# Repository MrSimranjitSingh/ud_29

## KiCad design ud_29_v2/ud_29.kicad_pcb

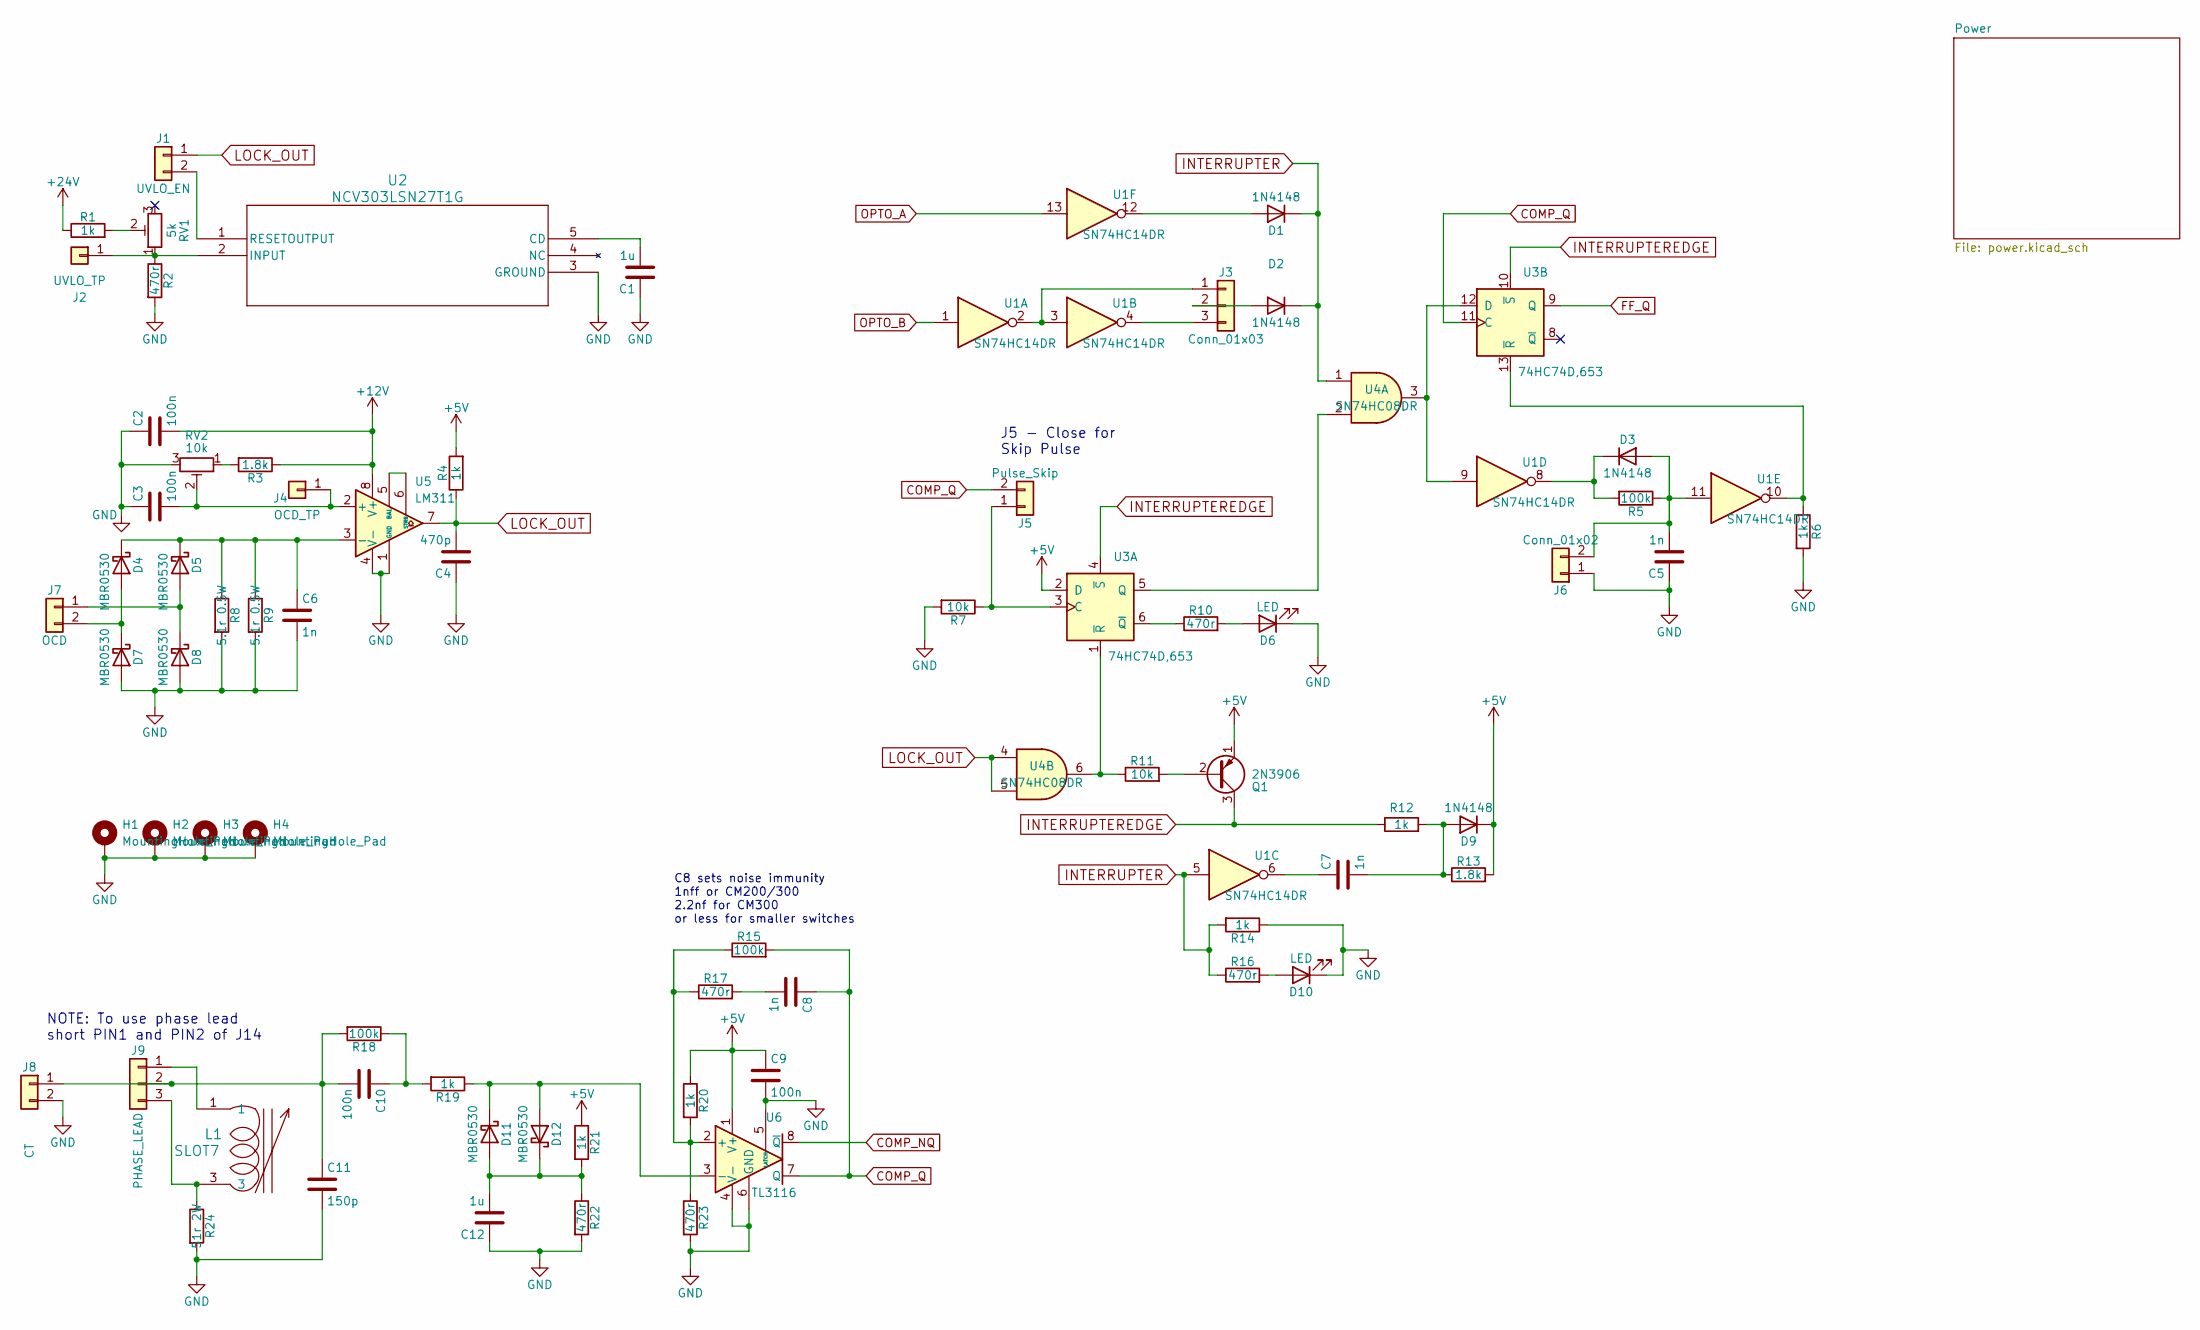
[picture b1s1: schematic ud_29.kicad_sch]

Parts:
C1, C12: 1u; C_1206_3216Metric_Pad1.33x1.80mm_HandSolder; Part Number CL21B105KBFNNNG
C2, C3, C9, C10: 100n; C_1206_3216Metric_Pad1.33x1.80mm_HandSolder; Part Number KGM21NR71H104KT
C4: 470p; C_1206_3216Metric_Pad1.33x1.80mm_HandSolder; Part Number C0805C471K5RAC7800
C5, C6, C7, C8: 1n; C_1206_3216Metric_Pad1.33x1.80mm_HandSolder; Part Number CL21B102KCANNNC
C11: 150p; C_1206_3216Metric_Pad1.33x1.80mm_HandSolder; Part Number C0805C151J5GAC7800
D1, D2, D3, D9: 1N4148; D_SOD-123; Part Number 1N4148WGW
D4, D5, D7, D8, D11, D12: MBR0530; D_SOD-123; Part Number MBR0530-TP
D6, D10: LED; LED_D5.0mm
H1, H2, H3, H4: MountingHole_Pad; MountingHole_3.5mm_Pad_TopBottom
J1: UVLO_EN; PinHeader_1x02_P2.54mm_Vertical
J2: UVLO_TP; PinHeader_1x01_P2.54mm_Vertical
J3: Conn_01x03; PinHeader_1x03_P2.54mm_Vertical
J4: OCD_TP; PinHeader_1x01_P2.54mm_Vertical
J5: Pulse_Skip; PinHeader_1x02_P2.54mm_Vertical
J6: Conn_01x02; PinHeader_1x02_P2.54mm_Vertical
J7: OCD; TerminalBlock_bornier-2_P5.08mm; Part Number EBB-02-D-BL
J8: CT; TerminalBlock_bornier-2_P5.08mm; Part Number EBB-02-D-BL
J9: PHASE_LEAD; PinHeader_1x03_P2.54mm_Vertical
L1: SLOT7; CoilCraft_Slot_7
Q1: 2N3906; TO-92
R1, R4, R6, R12, R14, R19, R20, R21: 1k; R_1206_3216Metric_Pad1.30x1.75mm_HandSolder; Part Number RNCP0805FTD1K00
R2, R10, R16, R17, R22, R23: 470r; R_1206_3216Metric_Pad1.30x1.75mm_HandSolder; Part Number RK73H2ATTD4700F
R3, R13: 1.8k; R_1206_3216Metric_Pad1.30x1.75mm_HandSolder; Part Number RK73B2ATTD182J
R5, R15, R18: 100k; R_1206_3216Metric_Pad1.30x1.75mm_HandSolder; Part Number RK73H2ATTD1003F
R7, R11: 10k; R_1206_3216Metric_Pad1.30x1.75mm_HandSolder; Part Number RK73H2ATTD1002F
R8, R9: 5.1r 0.5W; R_1206_3216Metric_Pad1.30x1.75mm_HandSolder; Part Number ESR10EZPJ5R1
R24: 51r 2W; R_1206_3216Metric_Pad1.30x1.75mm_HandSolder; Part Number CRM2512-JW-510ELF
RV1: 5k; Potentiometer_Bourns_3296W_Vertical
RV2: 10k; Potentiometer_Bourns_3296W_Vertical
U1: SN74HC14DR; SOIC-14_3.9x8.7mm_P1.27mm; Part Number SN74HC14DR
U2: NCV303LSN27T1G; TSOT-23-5_HandSoldering; Part Number NCV303LSN27T1G
U3: 74HC74D,653; SOIC-14_3.9x8.7mm_P1.27mm; Part Number 74HC74D,653
U4: SN74HC08DR; SOIC-14_3.9x8.7mm_P1.27mm; Part Number SN74HC08DR
U5: LM311; SOIC-8_3.9x4.9mm_P1.27mm; Part Number LM311DR
U6: TL3116; SOIC-8_3.9x4.9mm_P1.27mm; Part Number TL3116CD

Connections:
+5V: C9.1, D9.1 (K), Q1.1 (E), R4.2, R13.2, R20.1, R21.1, U3.2 (D), U6.1 (V+); also elsewhere on the board
+12V: C2.2, R3.1, U5.8 (V+); also elsewhere on the board
+24V: R1.1; also elsewhere on the board
COMP_NQ: U6.8 (~Q); also elsewhere on the board
COMP_Q: C8.1, J5.2, R15.2, U3.11 (C), U6.7 (Q); also elsewhere on the board
FF_Q: U3.9 (Q); also elsewhere on the board
GND: C1.1, C2.1, C3.1, C4.1, C5.1, C6.2, C9.2, C11.2, C12.1, D6.1 (K), D7.2 (A), D8.2 (A), D10.1 (K), H1.1, H2.1, H3.1, H4.1, J6.1, J8.2, R2.2, R6.2, R7.2, R8.2, R9.2, R14.1, R22.2, R23.2, R24.2, RV2.3, U2.3 (GROUND), U5.1 (GND), U5.4 (V-), U6.4 (V-), U6.5 (LATCH), U6.6 (GND); also elsewhere on the board
INTERRUPTER: D1.1 (K), D2.1 (K), R14.2, R16.1, U1.5, U4.1
INTERRUPTEREDGE: Q1.3 (C), R12.1, U3.4 (~S), U3.10 (~S)
LOCK_OUT: C4.2, J1.1, R4.1, U4.4, U4.5, U5.7
unnamed: C7.1, U1.6
unnamed: C8.2, R17.2
unnamed: C10.1, R18.1, R19.2
unnamed: D1.2 (A), U1.12
unnamed: D2.2 (A), J3.2
unnamed: C5.2, D3.2 (A), J6.2, R5.1, U1.11
unnamed: D3.1 (K), R5.2, U1.8
unnamed: D4.2 (A), D7.1 (K), J7.2
unnamed: C6.1, D4.1 (K), D5.1 (K), R8.1, R9.1, U5.3 (-)
unnamed: D5.2 (A), D8.1 (K), J7.1
unnamed: D6.2 (A), R10.2
unnamed: C7.2, D9.2 (A), R12.2, R13.1
unnamed: D10.2 (A), R16.2
unnamed: C12.2, D11.2 (A), D12.1 (K), R21.2, R22.1
unnamed: D11.1 (K), D12.2 (A), R19.1, U6.3 (-)
unnamed: J1.2, U2.1 (RESETOUTPUT)
unnamed: J2.1, R2.1, RV1.1, U2.2 (INPUT)
unnamed: J3.1, U1.2, U1.3
unnamed: J3.3, U1.4
unnamed: C3.2, J4.1, RV2.2, U5.2 (+)
unnamed: J5.1, R7.1, U3.3 (C)
unnamed: C10.2, C11.1, J8.1, J9.2, R18.2
unnamed: J9.1, L1.1
unnamed: J9.3, L1.3, R24.1
unnamed: Q1.2 (B), R11.2
unnamed: R1.2, RV1.2
unnamed: R3.2, RV2.1
unnamed: C1.2, U2.5 (CD)
unnamed: U3.5 (Q), U4.2
unnamed: R10.1, U3.6 (~Q)
unnamed: R11.1, U3.1 (~R), U4.6
unnamed: U1.9, U3.12 (D), U4.3
unnamed: R6.1, U1.10, U3.13 (~R)
unnamed: U5.5 (BAL), U5.6 (STRB)
unnamed: R15.1, R17.1, R20.2, R23.1, U6.2 (+)
OPTO_A: U1.13; also elsewhere on the board
OPTO_B: U1.1; also elsewhere on the board

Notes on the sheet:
C8 sets noise immunity 1nff or CM200/300 2.2nf for CM300 or less for smaller switches
NOTE: To use phase lead short PIN1 and PIN2 of J14
J5 - Close for Skip Pulse

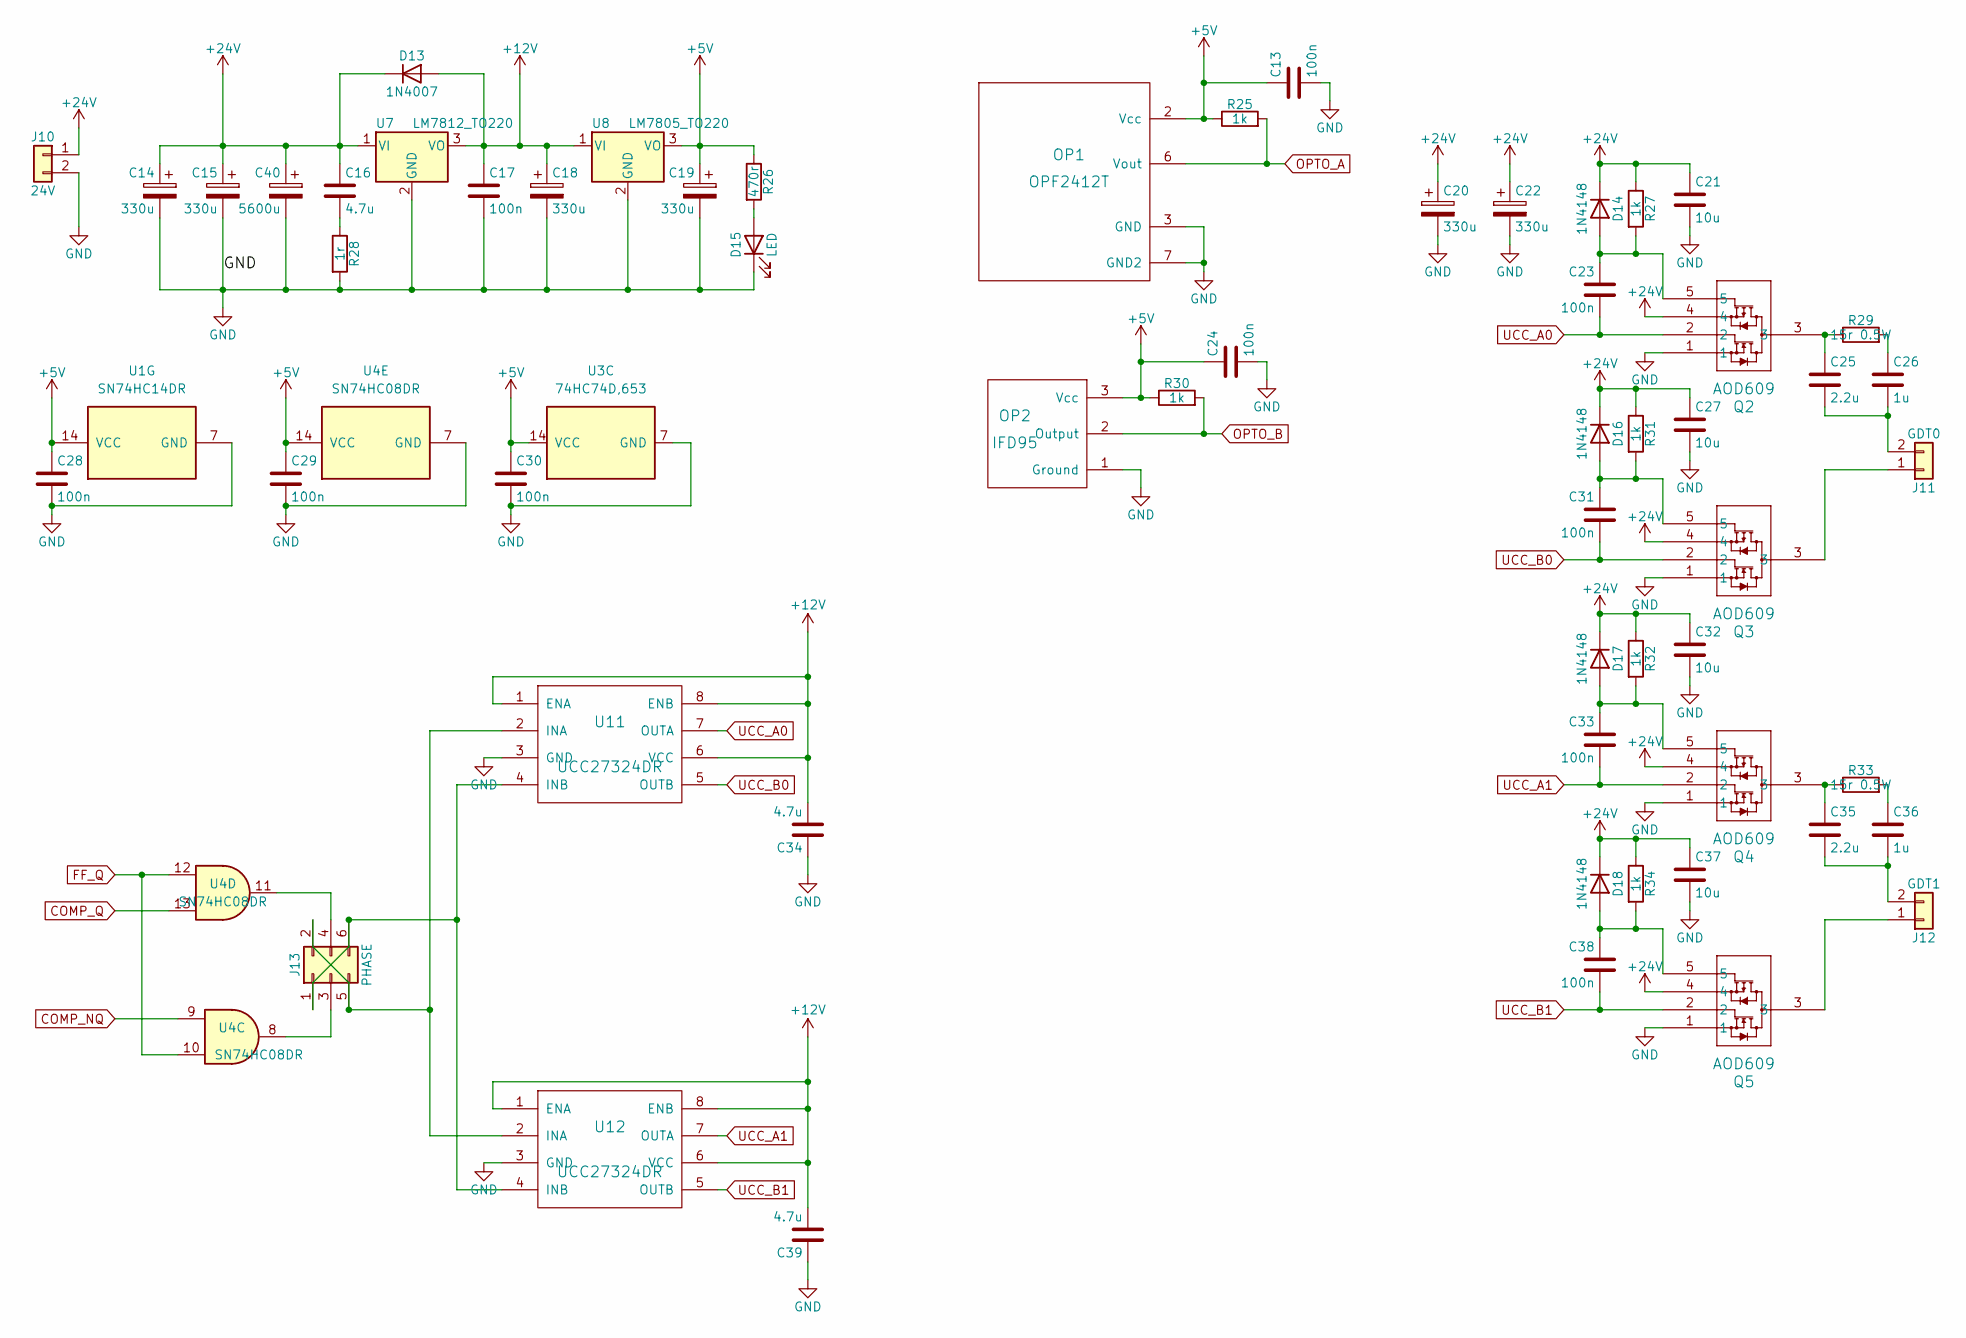
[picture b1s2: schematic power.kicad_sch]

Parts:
C13, C17, C23, C24, C28, C29, C30, C31, C33, C38: 100n; C_1206_3216Metric_Pad1.33x1.80mm_HandSolder; Part Number KGM21NR71H104KT
C14, C15, C18, C19, C20, C22: 330u; CP_Radial_D10.0mm_P5.00mm; Part Number EKYB350ELL331MH20D
C16, C34, C39: 4.7u; C_1206_3216Metric_Pad1.33x1.80mm_HandSolder; Part Number CL21A475KBQNNNE
C21, C27, C32, C37: 10u; C_1206_3216Metric_Pad1.33x1.80mm_HandSolder; Part Number GRM21BR61H106KE43L
C25, C35: 2.2u; C_1206_3216Metric_Pad1.33x1.80mm_HandSolder; Part Number CL21A225KBFNNNE
C26, C36: 1u; C_1206_3216Metric_Pad1.33x1.80mm_HandSolder; Part Number CL21B105KBFNNNG
C40: 5600u; CP_Radial_D18.0mm_P7.50mm; Part Number EKYB350ELL562MMP1S
D13: 1N4007; D_SOD-123; Part Number 1N4007FL
D14, D16, D17, D18: 1N4148; D_SOD-123; Part Number 1N4148WGW
D15: LED; LED_D5.0mm
J10: 24V; TerminalBlock_bornier-2_P5.08mm; Part Number EBB-02-D-BL
J11: GDT0; TerminalBlock_bornier-2_P5.08mm; Part Number EBB-02-D-BL
J12: GDT1; TerminalBlock_bornier-2_P5.08mm; Part Number EBB-02-D-BL
J13: PHASE; PinHeader_2x03_P2.54mm_Vertical
OP1: OPF2412T
OP2: IFD95
Q2, Q3, Q4, Q5: AOD609; TO-252-4; Part Number AOD609
R25, R27, R30, R31, R32, R34: 1k; R_1206_3216Metric_Pad1.30x1.75mm_HandSolder; Part Number RNCP0805FTD1K00
R26: 470r; R_1206_3216Metric_Pad1.30x1.75mm_HandSolder; Part Number RK73H2ATTD4700F
R28: 1r; R_1206_3216Metric_Pad1.30x1.75mm_HandSolder; Part Number RK73H2ATTD1R00F
R29, R33: 15r 0.5W; R_1206_3216Metric_Pad1.30x1.75mm_HandSolder; Part Number SG73P2ATTD15R0F
U1: SN74HC14DR; SOIC-14_3.9x8.7mm_P1.27mm; Part Number SN74HC14DR
U3: 74HC74D,653; SOIC-14_3.9x8.7mm_P1.27mm; Part Number 74HC74D,653
U4: SN74HC08DR; SOIC-14_3.9x8.7mm_P1.27mm; Part Number SN74HC08DR
U7: LM7812_TO220; TO-220-3_Vertical
U8: LM7805_TO220; TO-220-3_Vertical
U11, U12: UCC27324DR; SOIC-8_3.9x4.9mm_P1.27mm; Part Number UCC27324DR

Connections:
+5V: C13.1, C19.1, C24.1, C28.1, C29.1, C30.1, OP1.2 (Vcc), OP2.3 (Vcc), R25.1, R26.1, R30.1, U1.14 (VCC), U3.14 (VCC), U4.14 (VCC), U8.3 (VO); also elsewhere on the board
+12V: C17.1, C18.1, C34.2, C39.2, D13.2 (A), U7.3 (VO), U8.1 (VI), U11.1 (ENA), U11.6 (VCC), U11.8 (ENB), U12.1 (ENA), U12.6 (VCC), U12.8 (ENB); also elsewhere on the board
+24V: C14.1, C15.1, C16.1, C20.1, C21.1, C22.1, C27.1, C32.1, C37.1, C40.1, D13.1 (K), D14.1 (K), D16.1 (K), D17.1 (K), D18.1 (K), J10.1, Q2.4, Q3.4, Q4.4, Q5.4, R27.1, R31.1, R32.1, R34.1, U7.1 (VI); also elsewhere on the board
COMP_NQ: U4.9; also elsewhere on the board
COMP_Q: U4.13; also elsewhere on the board
FF_Q: U4.10, U4.12; also elsewhere on the board
GND: C13.2, C14.2, C15.2, C17.2, C18.2, C19.2, C20.2, C21.2, C22.2, C24.2, C27.2, C28.2, C29.2, C30.2, C32.2, C34.1, C37.2, C39.1, C40.2, D15.1 (K), J10.2, OP1.3 (GND), OP1.7 (GND2), OP2.1 (Ground), Q2.1, Q3.1, Q4.1, Q5.1, R28.2, U1.7 (GND), U3.7 (GND), U4.7 (GND), U7.2 (GND), U8.2 (GND), U11.3 (GND), U12.3 (GND); also elsewhere on the board
unnamed: C16.2, R28.1
unnamed: C25.1, Q2.3, R29.1
unnamed: C26.1, R29.2
unnamed: C35.1, Q4.3, R33.1
unnamed: C36.1, R33.2
unnamed: C23.1, D14.2 (A), Q2.5, R27.2
unnamed: D15.2 (A), R26.2
unnamed: C31.1, D16.2 (A), Q3.5, R31.2
unnamed: C33.1, D17.2 (A), Q4.5, R32.2
unnamed: C38.1, D18.2 (A), Q5.5, R34.2
unnamed: J11.1, Q3.3
unnamed: C25.2, C26.2, J11.2
unnamed: J12.1, Q5.3
unnamed: C35.2, C36.2, J12.2
unnamed: J13.1, J13.6, U11.4 (INB), U12.4 (INB)
unnamed: J13.2, J13.5, U11.2 (INA), U12.2 (INA)
unnamed: J13.3, U4.8
unnamed: J13.4, U4.11
OPTO_A: OP1.6 (Vout), R25.2; also elsewhere on the board
OPTO_B: OP2.2 (Output), R30.2; also elsewhere on the board
UCC_A0: C23.2, Q2.2, U11.7 (OUTA)
UCC_A1: C33.2, Q4.2, U12.7 (OUTA)
UCC_B0: C31.2, Q3.2, U11.5 (OUTB)
UCC_B1: C38.2, Q5.2, U12.5 (OUTB)

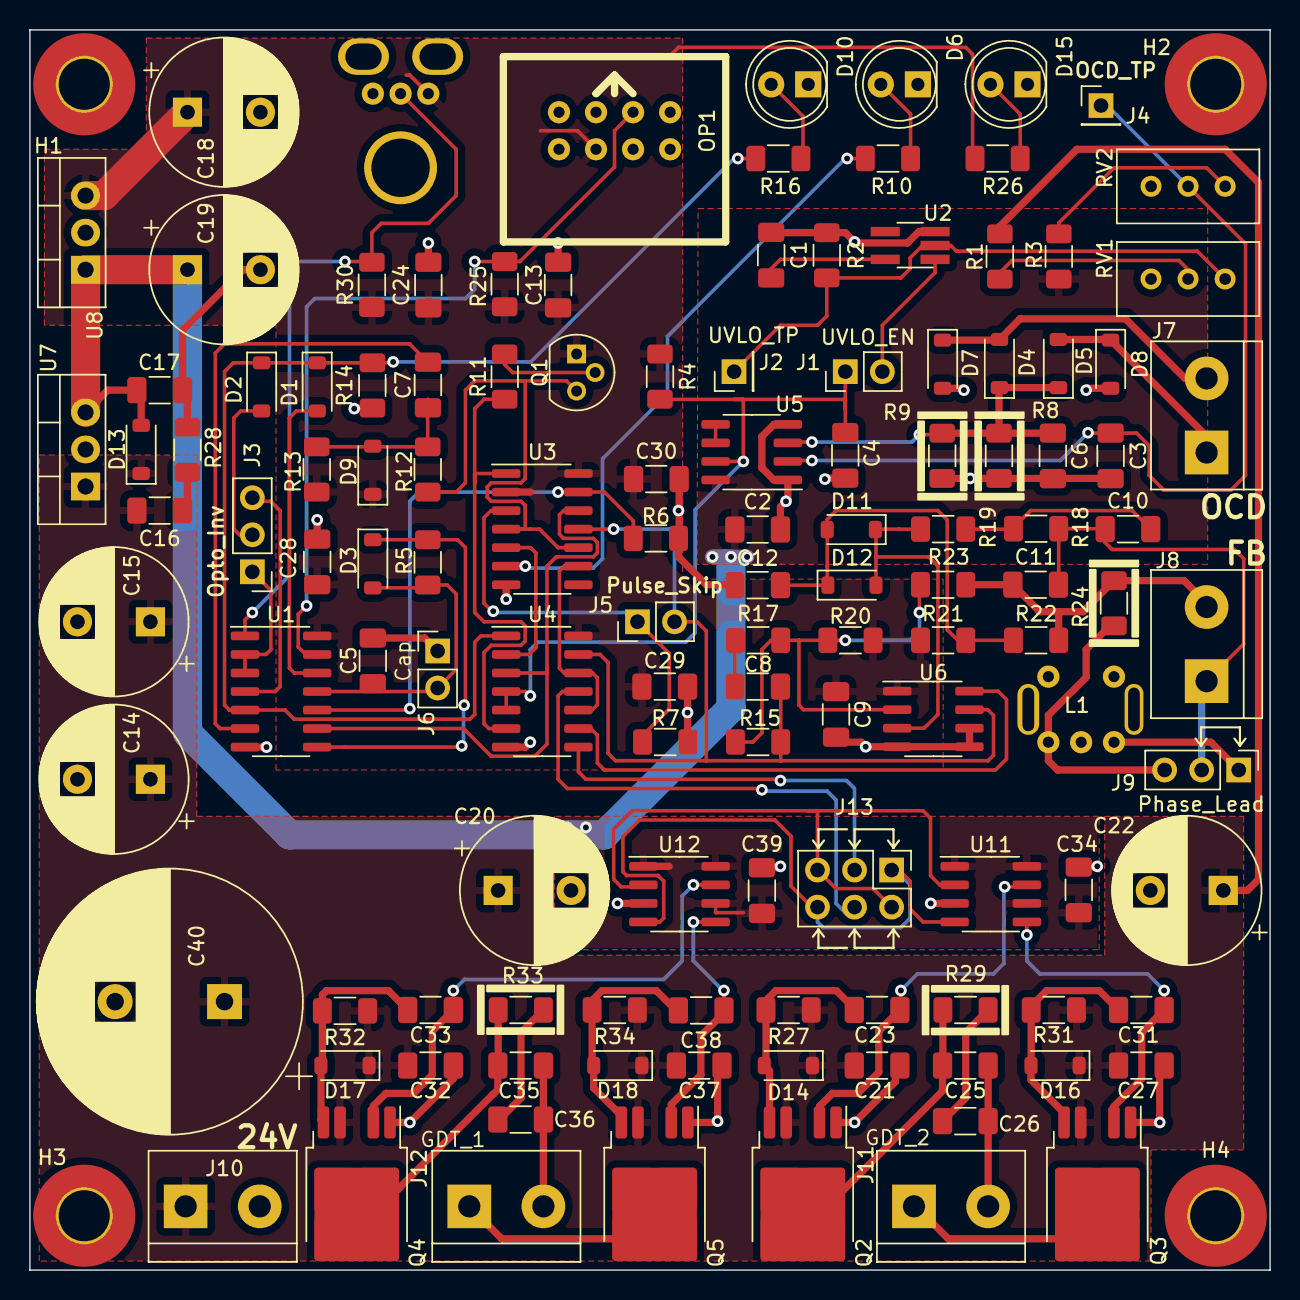
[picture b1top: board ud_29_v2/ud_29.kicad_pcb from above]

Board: 2 copper layers, 85.0 x 85.0 mm, 129 parts (1 on the bottom side), 69 nets.

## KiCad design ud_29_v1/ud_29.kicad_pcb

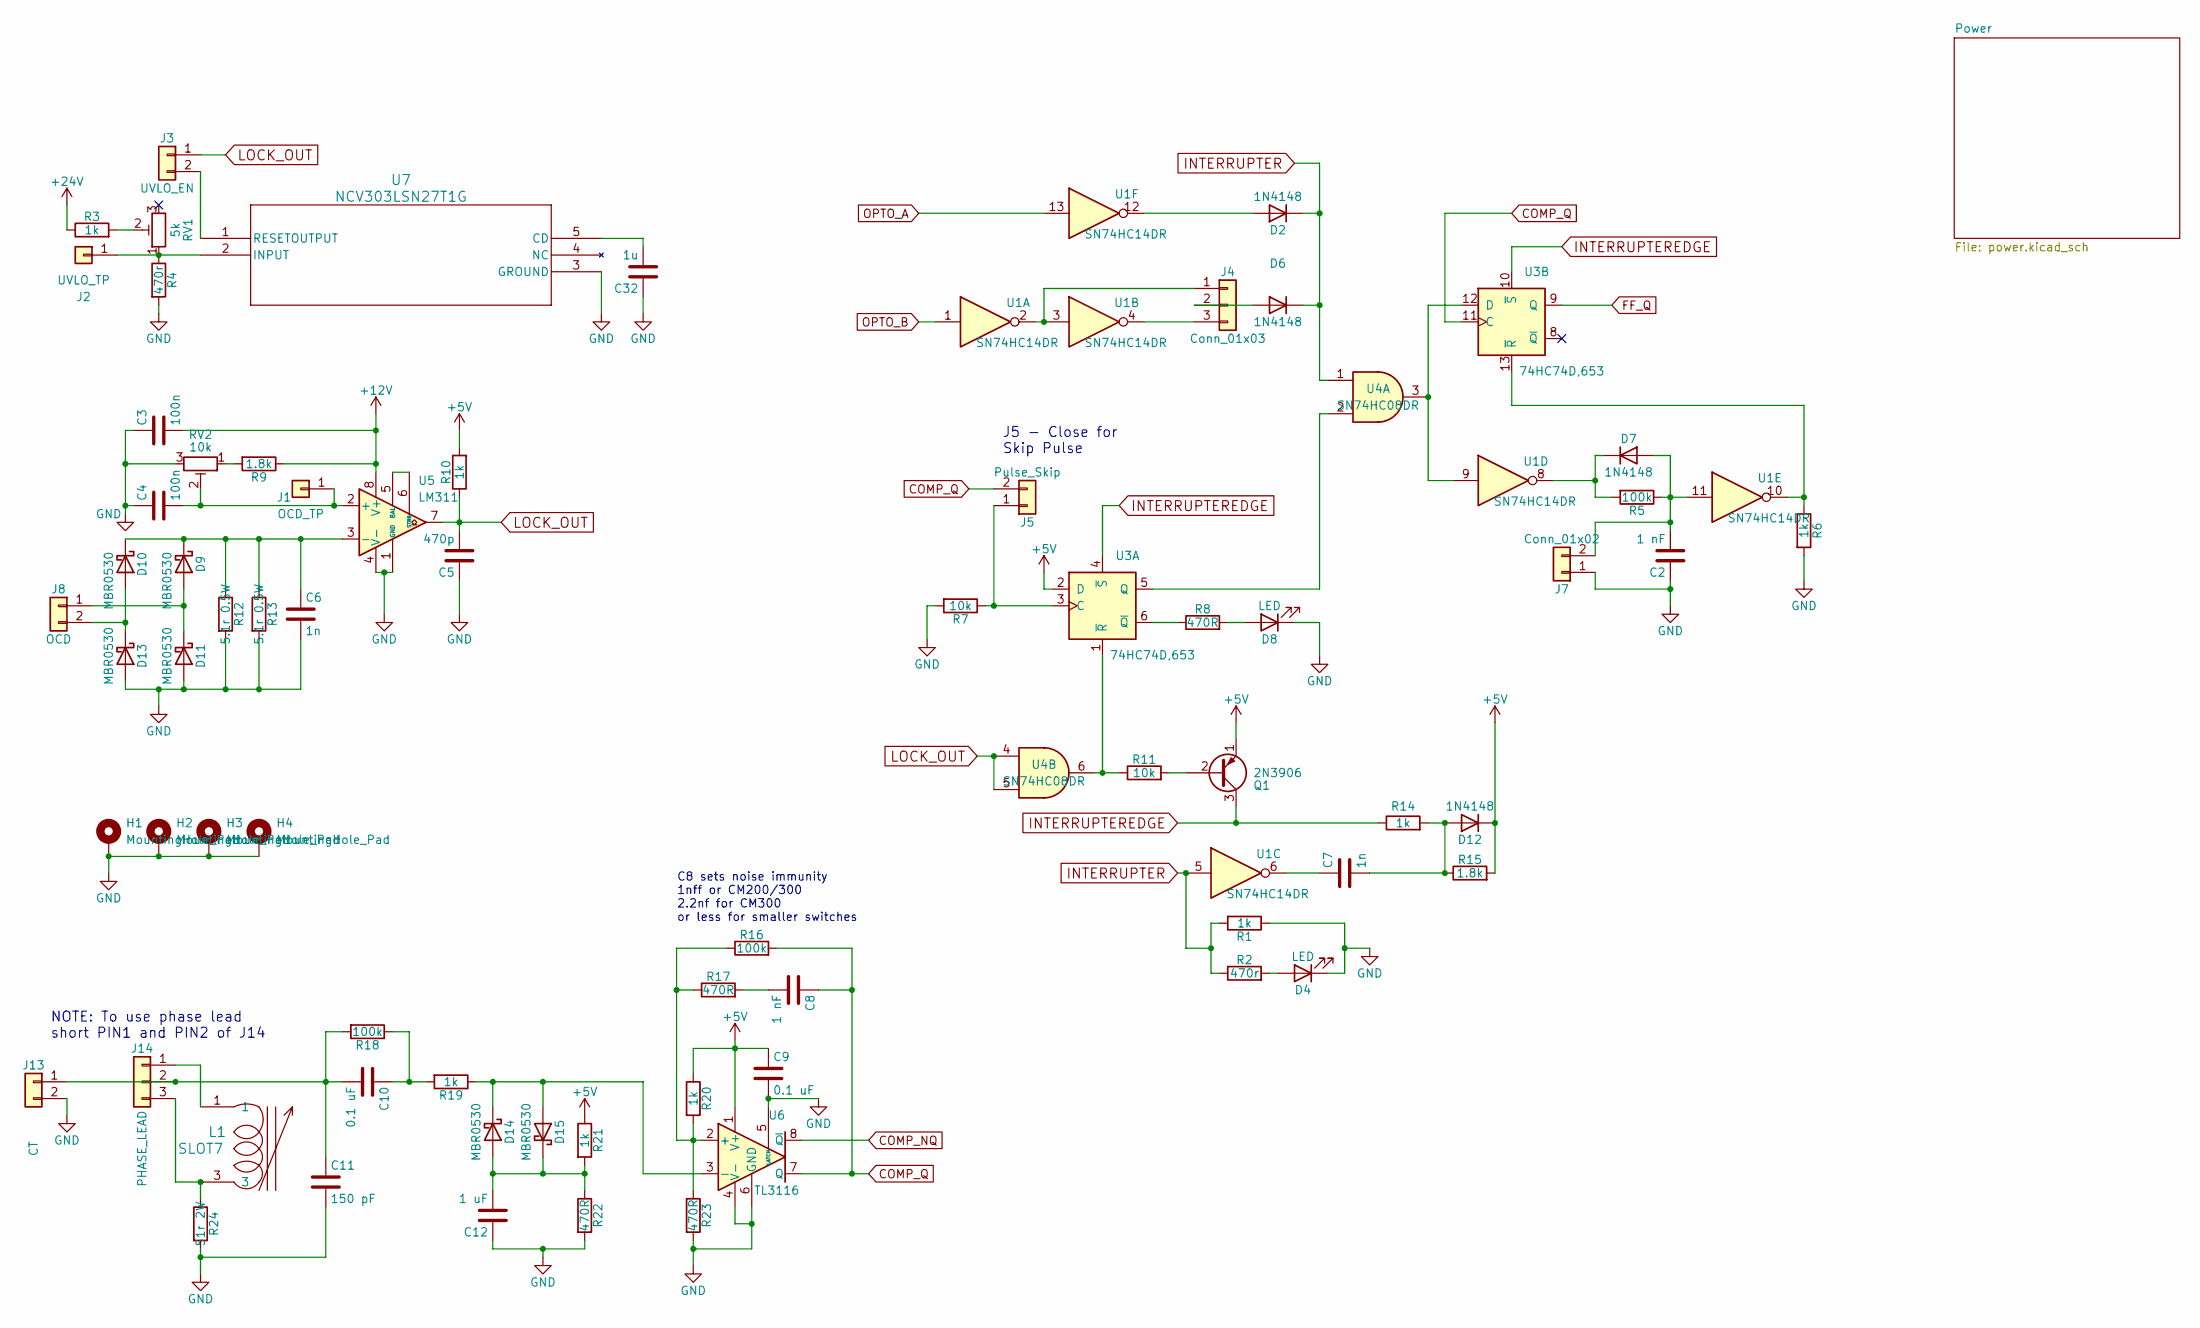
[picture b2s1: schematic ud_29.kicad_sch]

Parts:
C2, C8: 1 nF; C_1206_3216Metric_Pad1.33x1.80mm_HandSolder
C3, C4: 100n; C_1206_3216Metric_Pad1.33x1.80mm_HandSolder
C5: 470p; C_1206_3216Metric_Pad1.33x1.80mm_HandSolder
C6, C7: 1n; C_1206_3216Metric_Pad1.33x1.80mm_HandSolder
C9, C10: 0.1 uF; C_1206_3216Metric_Pad1.33x1.80mm_HandSolder
C11: 150 pF; C_1206_3216Metric_Pad1.33x1.80mm_HandSolder
C12: 1 uF; C_1206_3216Metric_Pad1.33x1.80mm_HandSolder
C32: 1u; C_1206_3216Metric_Pad1.33x1.80mm_HandSolder
D2, D6, D7, D12: 1N4148; D_SOD-123
D4, D8: LED; LED_D5.0mm
D9, D10, D11, D13, D14, D15: MBR0530; D_SOD-123
H1, H2, H3, H4: MountingHole_Pad; MountingHole_3.5mm_Pad_TopBottom
J1: OCD_TP; PinHeader_1x01_P2.54mm_Vertical
J2: UVLO_TP; PinHeader_1x01_P2.54mm_Vertical
J3: UVLO_EN; PinHeader_1x02_P2.54mm_Vertical
J4: Conn_01x03; PinHeader_1x03_P2.54mm_Vertical
J5: Pulse_Skip; PinHeader_1x02_P2.54mm_Vertical
J7: Conn_01x02; PinHeader_1x02_P2.54mm_Vertical
J8: OCD; TerminalBlock_bornier-2_P5.08mm
J13: CT; TerminalBlock_bornier-2_P5.08mm
J14: PHASE_LEAD; PinHeader_1x03_P2.54mm_Vertical
L1: SLOT7; CoilCraft_Slot_7
Q1: 2N3906; TO-92
R1, R3, R6, R10, R14, R19, R20, R21: 1k; R_1206_3216Metric_Pad1.30x1.75mm_HandSolder
R2, R4: 470r; R_1206_3216Metric_Pad1.30x1.75mm_HandSolder
R5, R16, R18: 100k; R_1206_3216Metric_Pad1.30x1.75mm_HandSolder
R7, R11: 10k; R_1206_3216Metric_Pad1.30x1.75mm_HandSolder
R8, R17, R22, R23: 470R; R_1206_3216Metric_Pad1.30x1.75mm_HandSolder
R9, R15: 1.8k; R_1206_3216Metric_Pad1.30x1.75mm_HandSolder
R12, R13: 5.1r 0.5W; R_1206_3216Metric_Pad1.30x1.75mm_HandSolder
R24: 51r 2W; R_1206_3216Metric_Pad1.30x1.75mm_HandSolder
RV1: 5k; Potentiometer_Bourns_3296W_Vertical
RV2: 10k; Potentiometer_Bourns_3296W_Vertical
U1: SN74HC14DR; SOIC-14_3.9x8.7mm_P1.27mm
U3: 74HC74D,653; SOIC-14_3.9x8.7mm_P1.27mm
U4: SN74HC08DR; SOIC-14_3.9x8.7mm_P1.27mm
U5: LM311; SOIC-8_3.9x4.9mm_P1.27mm
U6: TL3116; SOIC-8_3.9x4.9mm_P1.27mm
U7: NCV303LSN27T1G; TSOT-23-5_HandSoldering

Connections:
+5V: C9.1, D12.1 (K), Q1.1 (E), R10.2, R15.2, R20.1, R21.1, U3.2 (D), U6.1 (V+); also elsewhere on the board
+12V: C3.2, R9.1, U5.8 (V+); also elsewhere on the board
+24V: R3.1; also elsewhere on the board
COMP_NQ: U6.8 (~Q); also elsewhere on the board
COMP_Q: C8.1, J5.2, R16.2, U3.11 (C), U6.7 (Q); also elsewhere on the board
FF_Q: U3.9 (Q); also elsewhere on the board
GND: C2.1, C3.1, C4.1, C5.1, C6.2, C9.2, C11.2, C12.1, C32.1, D4.1 (K), D8.1 (K), D11.2 (A), D13.2 (A), H1.1, H2.1, H3.1, H4.1, J7.1, J13.2, R1.1, R4.2, R6.2, R7.2, R12.2, R13.2, R22.2, R23.2, R24.2, RV2.3, U5.1 (GND), U5.4 (V-), U6.4 (V-), U6.5 (LATCH), U6.6 (GND), U7.3 (GROUND); also elsewhere on the board
INTERRUPTER: D2.1 (K), D6.1 (K), R1.2, R2.1, U1.5, U4.1
INTERRUPTEREDGE: Q1.3 (C), R14.1, U3.4 (~S), U3.10 (~S)
LOCK_OUT: C5.2, J3.1, R10.1, U4.4, U4.5, U5.7
unnamed: C7.1, U1.6
unnamed: C8.2, R17.2
unnamed: C10.1, R18.1, R19.2
unnamed: D2.2 (A), U1.12
unnamed: D4.2 (A), R2.2
unnamed: D6.2 (A), J4.2
unnamed: C2.2, D7.2 (A), J7.2, R5.1, U1.11
unnamed: D7.1 (K), R5.2, U1.8
unnamed: D8.2 (A), R8.2
unnamed: D10.2 (A), D13.1 (K), J8.2
unnamed: C6.1, D9.1 (K), D10.1 (K), R12.1, R13.1, U5.3 (-)
unnamed: D9.2 (A), D11.1 (K), J8.1
unnamed: C7.2, D12.2 (A), R14.2, R15.1
unnamed: C12.2, D14.2 (A), D15.1 (K), R21.2, R22.1
unnamed: D14.1 (K), D15.2 (A), R19.1, U6.3 (-)
unnamed: C4.2, J1.1, RV2.2, U5.2 (+)
unnamed: J2.1, R4.1, RV1.1, U7.2 (INPUT)
unnamed: J3.2, U7.1 (RESETOUTPUT)
unnamed: J4.1, U1.2, U1.3
unnamed: J4.3, U1.4
unnamed: J5.1, R7.1, U3.3 (C)
unnamed: C10.2, C11.1, J13.1, J14.2, R18.2
unnamed: J14.1, L1.1
unnamed: J14.3, L1.3, R24.1
unnamed: Q1.2 (B), R11.2
unnamed: R3.2, RV1.2
unnamed: R9.2, RV2.1
unnamed: U3.5 (Q), U4.2
unnamed: R8.1, U3.6 (~Q)
unnamed: R11.1, U3.1 (~R), U4.6
unnamed: U1.9, U3.12 (D), U4.3
unnamed: R6.1, U1.10, U3.13 (~R)
unnamed: U5.5 (BAL), U5.6 (STRB)
unnamed 61: R16.1, R17.1, R20.2, R23.1, U6.2 (+); also elsewhere on the board
unnamed: C32.2, U7.5 (CD)
OPTO_A: U1.13; also elsewhere on the board
OPTO_B: U1.1; also elsewhere on the board

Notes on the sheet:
C8 sets noise immunity 1nff or CM200/300 2.2nf for CM300 or less for smaller switches
NOTE: To use phase lead short PIN1 and PIN2 of J14
J5 - Close for Skip Pulse

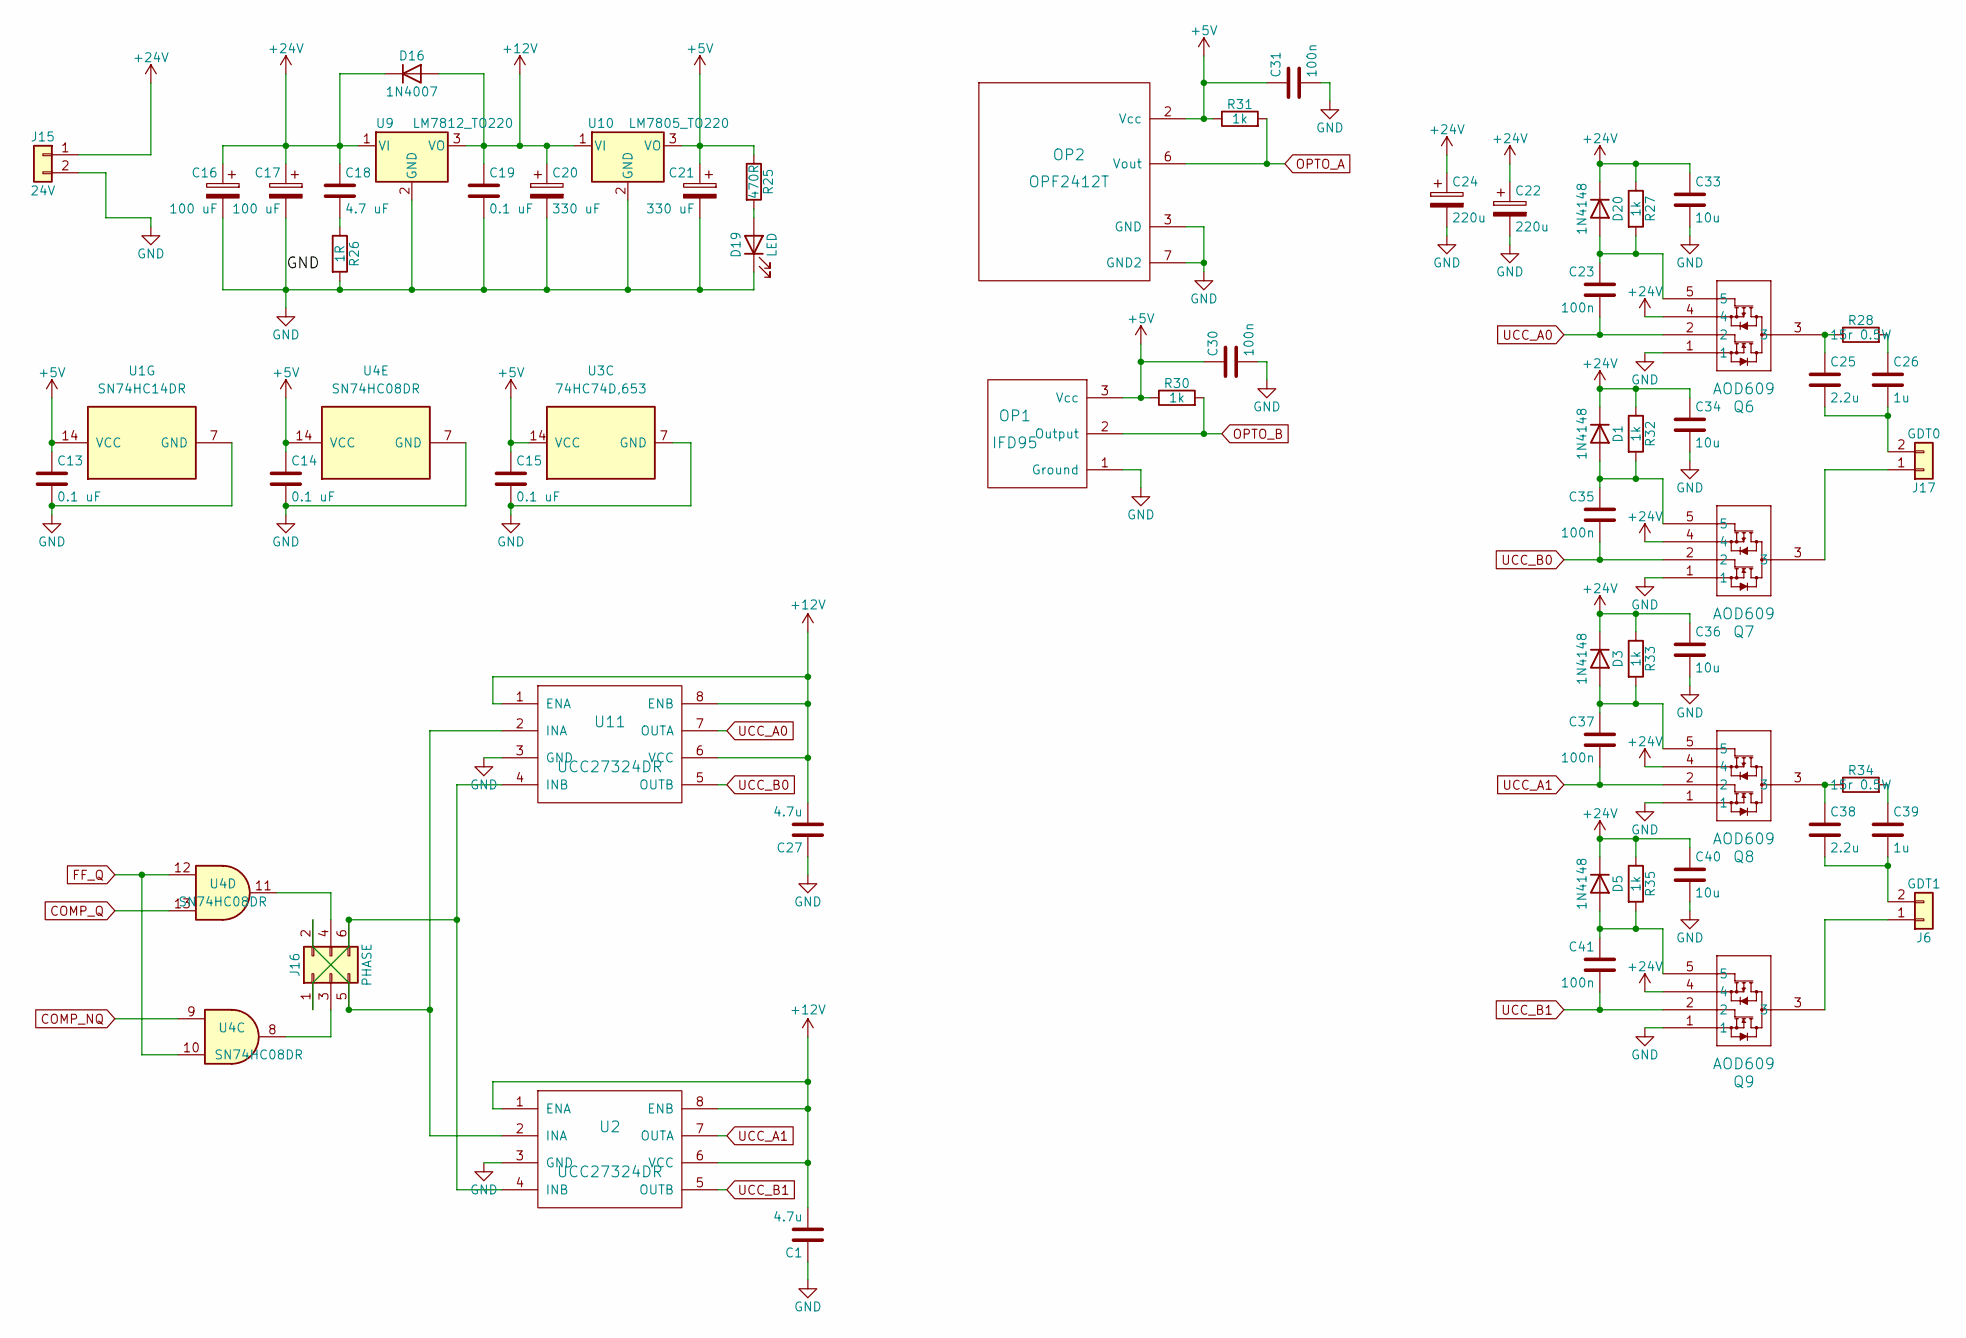
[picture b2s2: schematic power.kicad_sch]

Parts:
C1, C27: 4.7u; C_1206_3216Metric_Pad1.33x1.80mm_HandSolder
C13, C14, C15, C19: 0.1 uF; C_1206_3216Metric_Pad1.33x1.80mm_HandSolder
C16, C17: 100 uF; CP_Radial_D10.0mm_P5.00mm
C18: 4.7 uF; C_1206_3216Metric_Pad1.33x1.80mm_HandSolder
C20, C21: 330 uF; CP_Radial_D10.0mm_P5.00mm
C22, C24: 220u; CP_Radial_D10.0mm_P5.00mm
C23, C30, C31, C35, C37, C41: 100n; C_1206_3216Metric_Pad1.33x1.80mm_HandSolder
C25, C38: 2.2u; C_1206_3216Metric_Pad1.33x1.80mm_HandSolder
C26, C39: 1u; C_1206_3216Metric_Pad1.33x1.80mm_HandSolder
C33, C34, C36, C40: 10u; C_1206_3216Metric_Pad1.33x1.80mm_HandSolder
D1, D3, D5, D20: 1N4148; D_SOD-123
D16: 1N4007; D_SOD-123
D19: LED; LED_D5.0mm
J6: GDT1; TerminalBlock_bornier-2_P5.08mm
J15: 24V; TerminalBlock_bornier-2_P5.08mm
J16: PHASE; PinHeader_2x03_P2.54mm_Vertical
J17: GDT0; TerminalBlock_bornier-2_P5.08mm
OP1: IFD95
OP2: OPF2412T
Q6, Q7, Q8, Q9: AOD609; TO-252-4
R25: 470R; R_1206_3216Metric_Pad1.30x1.75mm_HandSolder
R26: 1R; R_1206_3216Metric_Pad1.30x1.75mm_HandSolder
R27, R30, R31, R32, R33, R35: 1k; R_1206_3216Metric_Pad1.30x1.75mm_HandSolder
R28, R34: 15r 0.5W; R_1206_3216Metric_Pad1.30x1.75mm_HandSolder
U1: SN74HC14DR; SOIC-14_3.9x8.7mm_P1.27mm
U2, U11: UCC27324DR; SOIC-8_3.9x4.9mm_P1.27mm
U3: 74HC74D,653; SOIC-14_3.9x8.7mm_P1.27mm
U4: SN74HC08DR; SOIC-14_3.9x8.7mm_P1.27mm
U9: LM7812_TO220; TO-220-3_Vertical
U10: LM7805_TO220; TO-220-3_Vertical

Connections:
+5V: C13.1, C14.1, C15.1, C21.1, C30.1, C31.1, OP1.3 (Vcc), OP2.2 (Vcc), R25.1, R30.1, R31.1, U1.14 (VCC), U3.14 (VCC), U4.14 (VCC), U10.3 (VO); also elsewhere on the board
+12V: C1.2, C19.1, C20.1, C27.2, D16.2 (A), U2.1 (ENA), U2.6 (VCC), U2.8 (ENB), U9.3 (VO), U10.1 (VI), U11.1 (ENA), U11.6 (VCC), U11.8 (ENB); also elsewhere on the board
+24V: C16.1, C17.1, C18.1, C22.1, C24.1, C33.1, C34.1, C36.1, C40.1, D1.1 (K), D3.1 (K), D5.1 (K), D16.1 (K), D20.1 (K), J15.1, Q6.4, Q7.4, Q8.4, Q9.4, R27.1, R32.1, R33.1, R35.1, U9.1 (VI); also elsewhere on the board
COMP_NQ: U4.9; also elsewhere on the board
COMP_Q: U4.13; also elsewhere on the board
FF_Q: U4.10, U4.12; also elsewhere on the board
GND: C1.1, C13.2, C14.2, C15.2, C16.2, C17.2, C19.2, C20.2, C21.2, C22.2, C24.2, C27.1, C30.2, C31.2, C33.2, C34.2, C36.2, C40.2, D19.1 (K), J15.2, OP1.1 (Ground), OP2.3 (GND), OP2.7 (GND2), Q6.1, Q7.1, Q8.1, Q9.1, R26.2, U1.7 (GND), U2.3 (GND), U3.7 (GND), U4.7 (GND), U9.2 (GND), U10.2 (GND), U11.3 (GND); also elsewhere on the board
unnamed: C18.2, R26.1
unnamed: C25.1, Q6.3, R28.1
unnamed: C26.1, R28.2
unnamed: C38.1, Q8.3, R34.1
unnamed: C39.1, R34.2
unnamed: C35.1, D1.2 (A), Q7.5, R32.2
unnamed: C37.1, D3.2 (A), Q8.5, R33.2
unnamed: C41.1, D5.2 (A), Q9.5, R35.2
unnamed: D19.2 (A), R25.2
unnamed: C23.1, D20.2 (A), Q6.5, R27.2
unnamed: J6.1, Q9.3
unnamed: C38.2, C39.2, J6.2
unnamed: J16.1, J16.6, U2.4 (INB), U11.4 (INB)
unnamed: J16.2, J16.5, U2.2 (INA), U11.2 (INA)
unnamed: J16.3, U4.8
unnamed: J16.4, U4.11
unnamed: J17.1, Q7.3
unnamed: C25.2, C26.2, J17.2
OPTO_A: OP2.6 (Vout), R31.2; also elsewhere on the board
OPTO_B: OP1.2 (Output), R30.2; also elsewhere on the board
UCC_A0: C23.2, Q6.2, U11.7 (OUTA)
UCC_A1: C37.2, Q8.2, U2.7 (OUTA)
UCC_B0: C35.2, Q7.2, U11.5 (OUTB)
UCC_B1: C41.2, Q9.2, U2.5 (OUTB)
